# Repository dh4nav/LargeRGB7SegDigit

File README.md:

# LargeRGB7SegDigit
A large WS2812B based 7 segment digit

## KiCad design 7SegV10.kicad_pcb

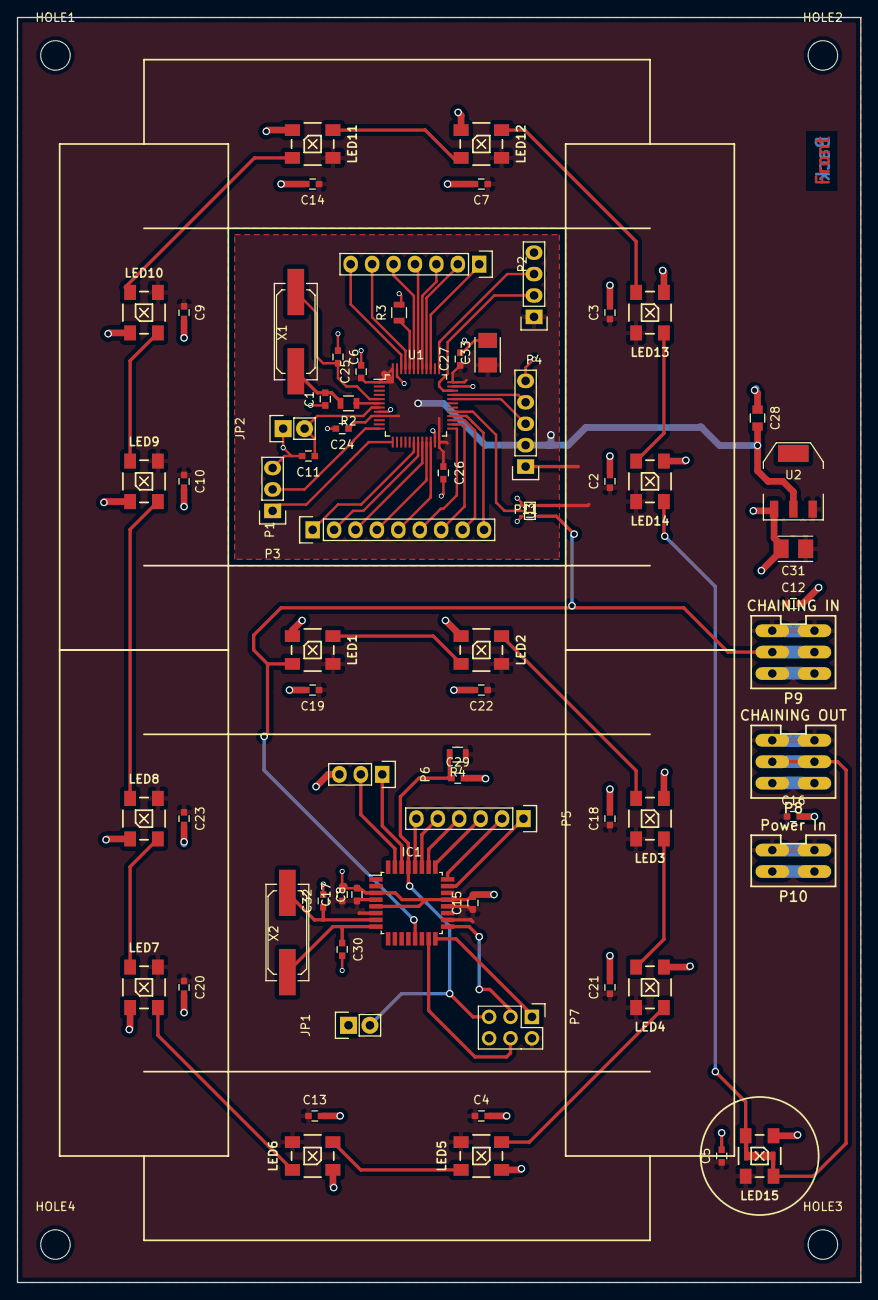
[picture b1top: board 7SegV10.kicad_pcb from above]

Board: 2 copper layers, 100.0 x 150.0 mm, 74 parts (0 on the bottom side), 61 nets.

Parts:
C1, C6: 12p; C_0603
C2, C3, C4, C5, C7, C8, C9, C10, C11, C12, C13, C14, C15, C16, C17, C18, C19, C20, C21, C22, C23, C24, C25, C26, C27, C29: 100n; C_0603
C28: 1µ; C_0805
C30, C32: 22p; C_0603
C31, C33: 10µ; TantalC_SizeB_EIA-3528_Reflow
HOLE1, HOLE2, HOLE3, HOLE4: MountingHole_3-5mm
IC1: ATMEGA328-A; TQFP-32_7x7mm_Pitch0.8mm
JP1: RESET AVR; Pin_Header_Straight_1x02
JP2: RESET STM32; Pin_Header_Straight_1x02
LED1, LED2, LED3, LED4, LED5, LED6, LED7, LED8, LED9, LED10, LED11, LED12, LED13, LED14: WS2812B
LED15: WS2812B; WS2812B_data-bridgeable
P1: GPIO1 STM32; Pin_Header_Straight_1x09
P2: GPIO2 STM32; Pin_Header_Straight_1x07
P3: RS232 STM32; Pin_Header_Straight_1x03
P4: SWD; Pin_Header_Straight_1x04
P5: GPIO1 AVR; Pin_Header_Straight_1x06
P6: RS232 AVR; Pin_Header_Straight_1x03
P7: ISP; Pin_Header_Straight_2x03
P8: CHAINING OUT; WAGO233-3
P9: CHAINING IN; WAGO233-3
P10: Power In; WAGO233-2
P11: USB STM32; Pin_Header_Straight_1x05
R2: 390R; R_0805
R3: R_Small; R_0805
R4: 10k; R_0805
U1: STM32F103C8; LQFP-48_7x7mm_Pitch0.5mm
U2: NCP1117ST33T3G; SOT-223
U3: 74AHCT1G125; SOT-353
X1: 8MHz; Q_49U3HMS
X2: 16MHz; Q_49U3HMS

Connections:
+3V3: C24.1, C25.1, C26.1, C27.1, C28.2, C33.1, P4.1, P11.2, U1.1, U1.9, U1.24, U1.36, U1.48, U2.2
+5V: C2.1, C3.1, C4.1, C5.1, C7.1, C8.1, C9.1, C10.1, C12.1, C13.1, C14.1, C15.1, C16.1, C17.1, C18.1, C19.1, C20.1, C21.1, C22.1, C23.1, C31.1, IC1.4, IC1.6, IC1.18, IC1.20, LED1.1, LED2.1, LED3.1, LED4.1, LED5.1, LED6.1, LED7.1, LED8.1, LED9.1, LED10.1, LED11.1, LED12.1, LED13.1, LED14.1, LED15.1, P7.2, P8.1, P9.1, P10.1, P11.1, R4.1, U2.3, U3.5
GND: C1.1, C2.2, C3.2, C4.2, C5.2, C6.1, C7.2, C8.2, C9.2, C10.2, C11.2, C12.2, C13.2, C14.2, C15.2, C16.2, C17.2, C18.2, C19.2, C20.2, C21.2, C22.2, C23.2, C24.2, C25.2, C26.2, C27.2, C28.1, C29.2, C30.2, C31.2, C32.2, C33.2, IC1.3, IC1.5, IC1.21, JP1.1, JP2.1, LED1.3, LED2.3, LED3.3, LED4.3, LED5.3, LED6.3, LED7.3, LED8.3, LED9.3, LED10.3, LED11.3, LED12.3, LED13.3, LED14.3, LED15.3, P3.3, P4.4, P6.3, P7.6, P8.3, P9.3, P10.2, P11.5, R3.2, U1.8, U1.23, U1.35, U1.47, U2.1, U3.1, U3.3
LEDS_IN: IC1.13, LED1.4, P9.2, U3.4
LEDS_IN_3.3V: U1.29, U3.2
LEDS_OUT: LED15.2, P8.2
unnamed: C1.2, R2.2, X1.1
unnamed: C6.2, U1.5, X1.2
unnamed: C30.1, IC1.8, X2.1
unnamed: C32.1, IC1.7, X2.2
unnamed: IC1.15, P7.4
unnamed: IC1.16, P7.1
unnamed: IC1.17, P7.3
unnamed: IC1.23, P5.1
unnamed: IC1.24, P5.2
unnamed: IC1.25, P5.3
unnamed: IC1.26, P5.4
unnamed: IC1.27, P5.5
unnamed: IC1.28, P5.6
unnamed: IC1.30, P6.1
unnamed: IC1.31, P6.2
unnamed: LED1.2, LED2.4
unnamed: LED2.2, LED3.4
unnamed: LED3.2, LED4.4
unnamed: LED4.2, LED5.4
unnamed: LED5.2, LED6.4
unnamed: LED6.2, LED7.4
unnamed: LED7.2, LED8.4
unnamed: LED8.2, LED9.4
unnamed: LED10.2, LED11.4
unnamed: LED9.2, LED10.4
unnamed: LED11.2, LED12.4
unnamed: LED12.2, LED13.4
unnamed: LED13.2, LED14.4
unnamed: LED14.2, LED15.4
unnamed: P1.1, U1.18
unnamed: P1.2, U1.19
unnamed: P1.3, U1.20
unnamed: P1.4, U1.21
unnamed: P1.5, U1.22
unnamed: P1.6, U1.25
unnamed: P1.7, U1.26
unnamed: P1.8, U1.27
unnamed: P1.9, U1.28
unnamed: P2.1, U1.39
unnamed: P2.2, U1.40
unnamed: P2.3, U1.41
unnamed: P2.4, U1.42
unnamed: P2.5, U1.43
unnamed: P2.6, U1.45
unnamed: P2.7, U1.46
unnamed: P3.1, U1.13
unnamed: P3.2, U1.12
unnamed: P4.2, U1.34
unnamed: P4.3, U1.37
unnamed: R2.1, U1.6
unnamed: R3.1, U1.44
RESET_AVR: C29.1, IC1.29, JP1.2, P7.5, R4.2
RESET_STM32: C11.1, JP2.2, U1.7
USBDM: P11.3, U1.32
USBDP: P11.4, U1.33

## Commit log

2015-10-12 init commit. WS2812B library imported from https://github.com/madworm/WS2812B.pretty
2015-12-03 new version
